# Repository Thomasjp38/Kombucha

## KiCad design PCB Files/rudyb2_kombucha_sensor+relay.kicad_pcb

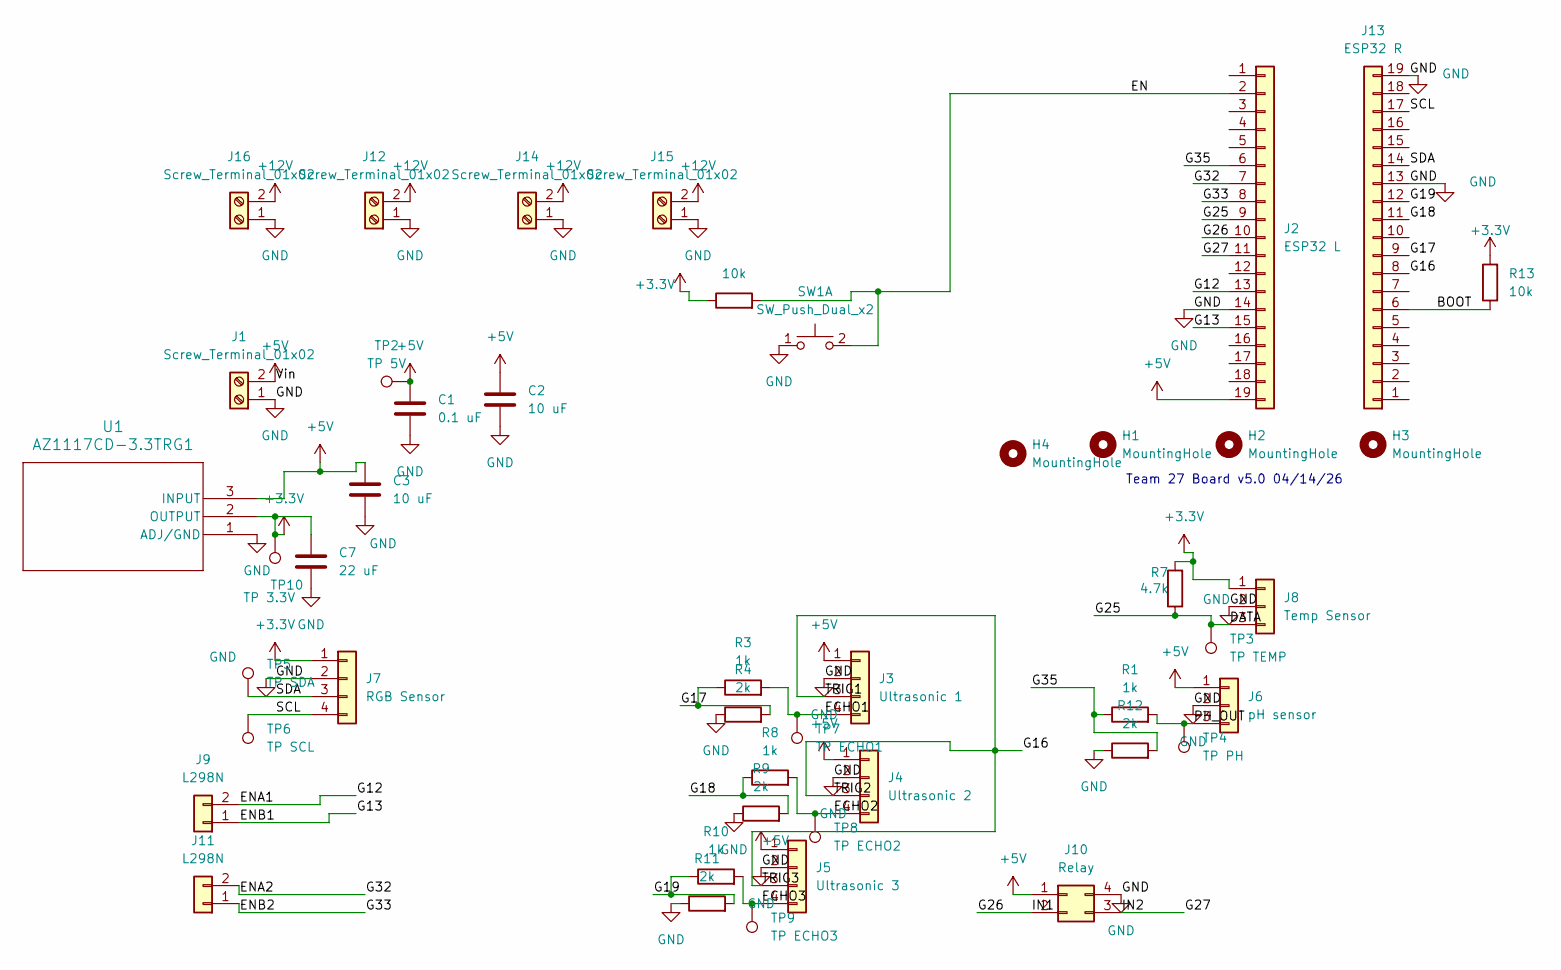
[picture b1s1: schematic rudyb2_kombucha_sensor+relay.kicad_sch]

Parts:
C1: 0.1 uF; C_0805_2012Metric_Pad1.18x1.45mm_HandSolder
C2, C3: 10 uF; C_0805_2012Metric_Pad1.18x1.45mm_HandSolder
C7: 22 uF; C_0805_2012Metric_Pad1.18x1.45mm_HandSolder
H1, H2, H3, H4: MountingHole; MountingHole_3.2mm_M3
J1, J12, J14, J15, J16: Screw_Terminal_01x02; TerminalBlock_Xinya_XY308-2.54-2P_1x02_P2.54mm_Horizontal
J2: ESP32 L; Molex_SL_171971-0019_1x19_P2.54mm_Vertical
J3: Ultrasonic 1; Molex_KK-254_AE-6410-04A_1x04_P2.54mm_Vertical
J4: Ultrasonic 2; Molex_KK-254_AE-6410-04A_1x04_P2.54mm_Vertical
J5: Ultrasonic 3; Molex_KK-254_AE-6410-04A_1x04_P2.54mm_Vertical
J6: pH sensor; Molex_KK-254_AE-6410-03A_1x03_P2.54mm_Vertical
J7: RGB Sensor; Molex_KK-254_AE-6410-04A_1x04_P2.54mm_Vertical
J8: Temp Sensor; Molex_KK-254_AE-6410-03A_1x03_P2.54mm_Vertical
J9, J11: L298N; Molex_KK-254_AE-6410-02A_1x02_P2.54mm_Vertical
J10: Relay; Molex_Micro-Fit_3.0_43045-0400_2x02_P3.00mm_Horizontal
J13: ESP32 R; Molex_SL_171971-0019_1x19_P2.54mm_Vertical
R1, R3, R8, R10: 1k; R_0805_2012Metric_Pad1.20x1.40mm_HandSolder
R2, R13: 10k; R_0805_2012Metric_Pad1.20x1.40mm_HandSolder
R4, R9, R11, R12: 2k; R_0805_2012Metric_Pad1.20x1.40mm_HandSolder
R7: 4.7k; R_0805_2012Metric_Pad1.20x1.40mm_HandSolder
SW1: SW_Push_Dual_x2; SW_SPST_B3S-1000
TP2: TP 5V; TestPoint_Pad_D1.5mm
TP3: TP TEMP; TestPoint_Pad_D1.5mm
TP4: TP PH; TestPoint_Pad_D1.5mm
TP5: TP SDA; TestPoint_Pad_D1.5mm
TP6: TP SCL; TestPoint_Pad_D1.5mm
TP7: TP ECHO1; TestPoint_Pad_D1.5mm
TP8: TP ECHO2; TestPoint_Pad_D1.5mm
TP9: TP ECHO3; TestPoint_Pad_D1.5mm
TP10: TP 3.3V; TestPoint_Pad_D1.5mm
U1: AZ1117CD-3.3TRG1; DPAK457P1010X238-3N

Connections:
+3.3V: C7.1, J7.1, J8.1, R2.1, R7.2, R13.2, TP10.1, U1.2 (OUTPUT)
+5V: C1.1, C2.1, C3.1, J1.2, J2.19, J3.1, J4.1, J5.1, J6.1, J10.1, TP2.1, U1.3 (INPUT)
+12V: J12.2, J14.2, J15.2, J16.2
/BOOT: J13.6, R13.1
/DATA: J2.9, J8.3, R7.1, TP3.1
/ECHO1: J3.4, R3.2, TP7.1
/ECHO2: J4.4, R8.2, TP8.1
/ECHO3: J5.4, R10.2, TP9.1
/EN: J2.2, R2.2, SW1.2 (D)
/ENA1: J2.13, J9.2
/ENA2: J2.7, J11.2
/ENB1: J2.15, J9.1
/ENB2: J2.8, J11.1
/G16: J3.3, J4.3, J5.3, J13.8
/G17: J13.9, R3.1, R4.2
/G18: J13.11, R8.1, R9.2
/G19: J13.12, R10.1, R11.2
/G26: J2.10, J10.2
/G27: J2.11, J10.3
/G35: J2.6, R1.1, R12.2
/PH_OUT: J6.3, R1.2, TP4.1
/SCL: J7.4, J13.17, TP6.1
/SDA: J7.3, J13.14, TP5.1
GND: C1.2, C2.2, C3.2, C7.2, J1.1, J2.14, J3.2, J4.2, J5.2, J6.2, J7.2, J8.2, J10.4, J12.1, J13.13, J13.19, J14.1, J15.1, J16.1, R4.1, R9.1, R11.1, R12.1, SW1.1 (C), U1.1 (ADJ/GND)

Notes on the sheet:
Team 27 Board v5.0 04/14/26

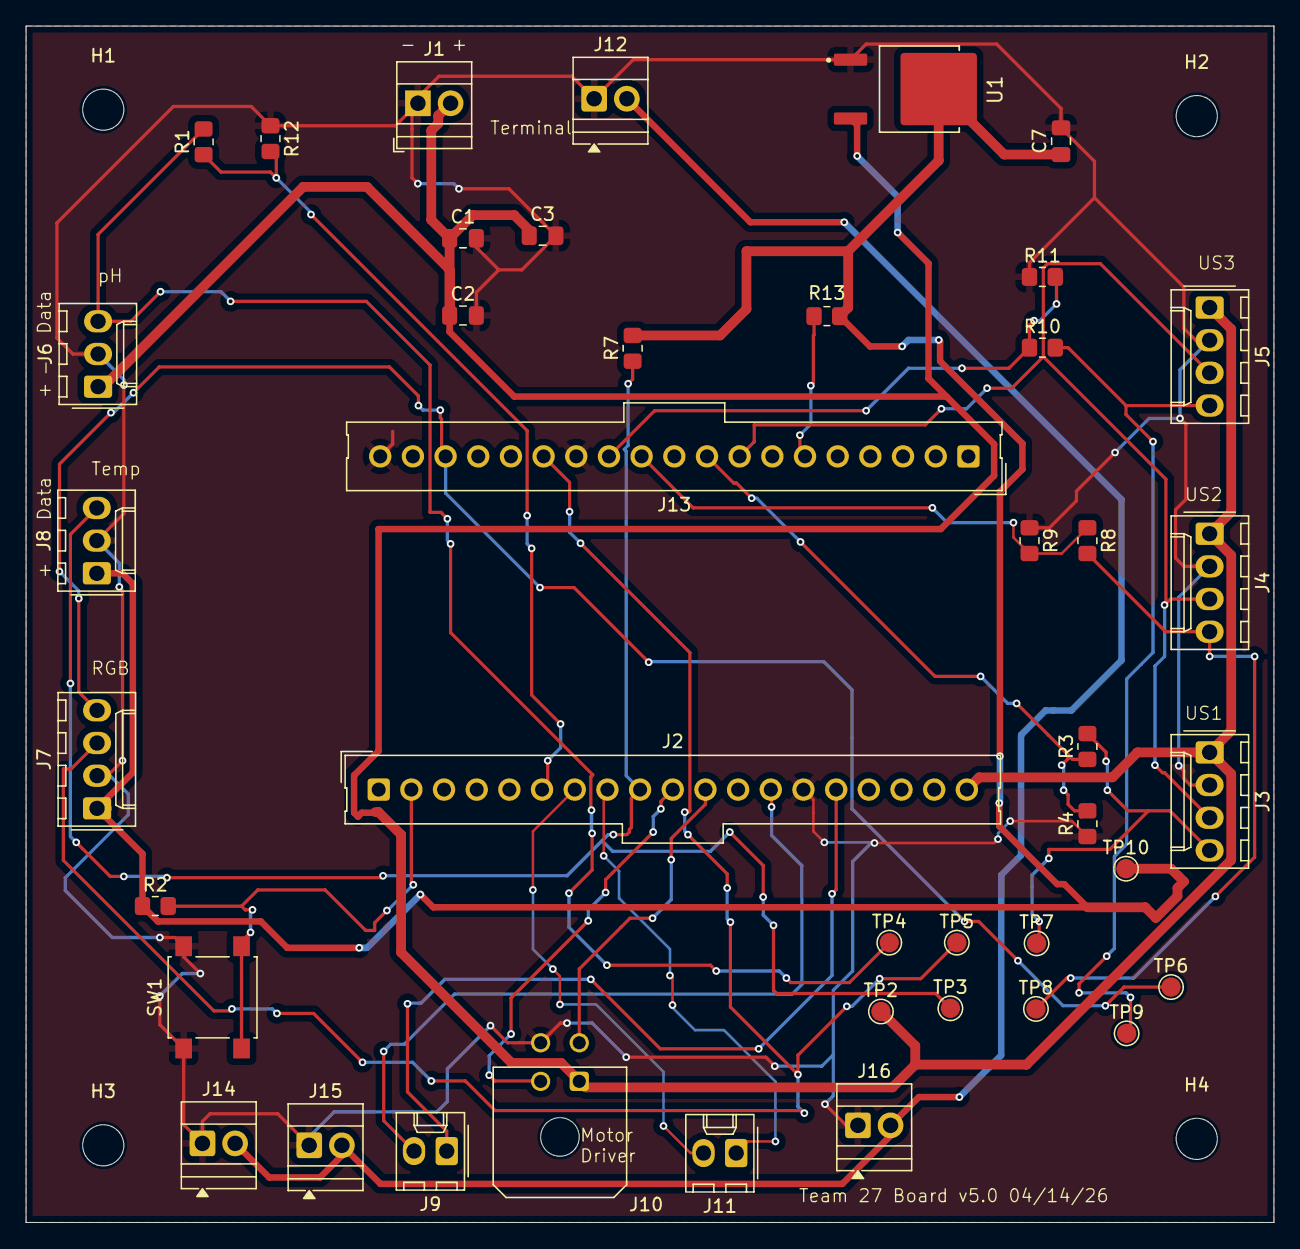
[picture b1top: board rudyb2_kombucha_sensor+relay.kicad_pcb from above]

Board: 2 copper layers, 97.0 x 93.0 mm, 46 parts (0 on the bottom side), 24 nets.

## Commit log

2026-02-17 Create README.md
    Hi
2026-02-17 Create README.md
    yolo
2026-02-18 Update README.md
    New designs for convenience
2026-02-18 Add files via upload
    Fermentation System Prototype
2026-02-18 Update README.md
    added prototype image to Readme
2026-02-20 Add files via upload
    Notes for Power Subsytem
2026-02-20 Add files via upload
    Initial code for read US sensors, with added multiplexing feature. Confirmed working.
2026-02-20 Rename KombuchaSensors to Code
2026-02-20 Rename KombuchaSensors.ino to code/KombuchaSensors.ino
2026-02-25 Temp sensor successfully working
2026-02-25 Pump stand/jar
2026-02-27 Motor controller for peristaltic pumps operational
2026-03-03 Improve sensor read efficiency with quiet-time gating and cached connection checks
2026-03-25 Create PCB Files
2026-03-25 Update PCB Files
2026-03-31 Add organized TCS34725 color module with HSL output
2026-04-02 Rename Kombucha Fermentation Design Document (1).pdf to Documents/Kombucha Fermentation Design Document (1).pdf
2026-05-08 Add files via upload
    added schematic and PCB
